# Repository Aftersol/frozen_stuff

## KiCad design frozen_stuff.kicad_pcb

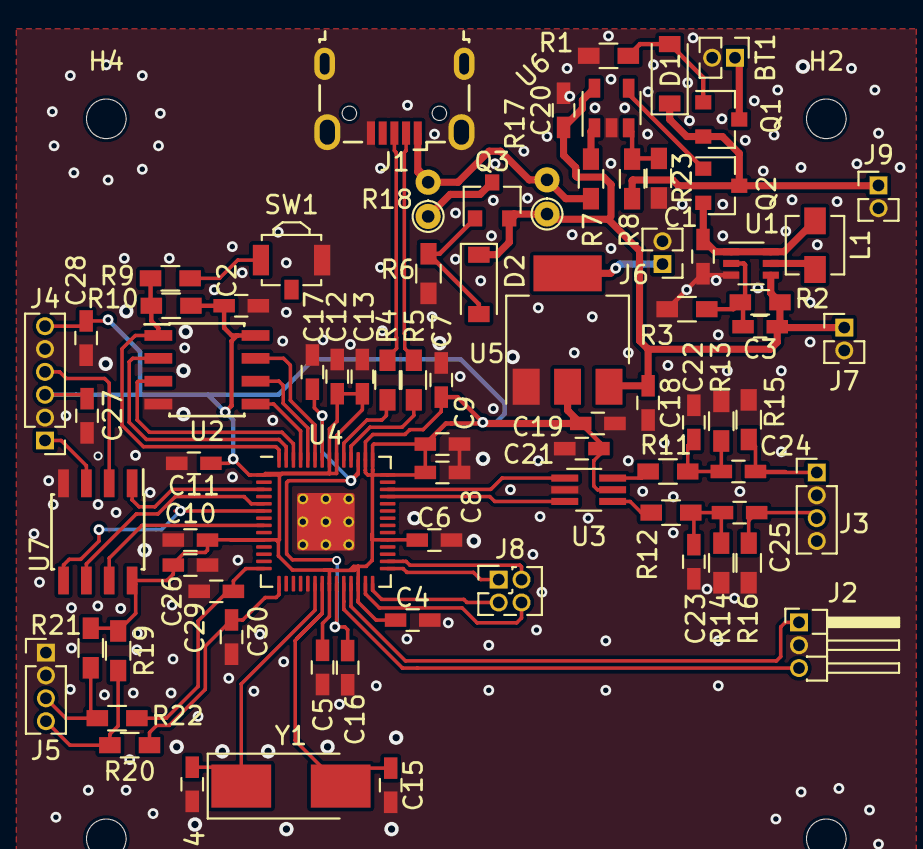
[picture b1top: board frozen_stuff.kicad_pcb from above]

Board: 2 copper layers, 82 parts (0 on the bottom side), 53 nets.

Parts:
BT1: AA; Pin_Header_Straight_1x02_Pitch1.27mm
C1, C3, C18: 10µ; C_0603_HandSoldering
C2, C4, C5, C6, C7, C8, C9, C10, C11, C12, C13, C16, C17, C20, C21, C22, C23, C26, C27, C28, C29, C30: 0.1µ; C_0603_HandSoldering
C14, C15: 22p; C_0603_HandSoldering
C19: 22µ; C_0603_HandSoldering
C24, C25: 47µ; C_0603_HandSoldering
D1, D2: D; D_SOD-123
H1, H2, H3, H4: MountingHole; MountingHole_2.2mm_M2
J1: USB_B_Micro; USB_Micro-B_Wuerth-629105150521
J2: SWD; Pin_Header_Angled_1x03_Pitch1.27mm
J3: Conn_01x04; Pin_Header_Straight_1x04_Pitch1.27mm
J4: Conn_01x06; Pin_Header_Straight_1x06_Pitch1.27mm
J5: Buttons; Pin_Header_Straight_1x04_Pitch1.27mm
J6, J7, J9: Conn_01x02; Pin_Header_Straight_1x02_Pitch1.27mm
J8: Conn_02x02_Top_Bottom; Pin_Header_Straight_2x02_Pitch1.27mm
L1: 4.7µH; L_Vishay_IHLP-1212
Q1, Q2, Q3: NTR2101P; SOT-23
R1, R6, R8, R19, R21, R23: 10K; R_0603_HandSoldering
R2: 0; R_0603_HandSoldering
R3, R10: DNF; R_0603_HandSoldering
R4, R5: 27; R_0603_HandSoldering
R7, R9, R20, R22: 1K; R_0603_HandSoldering
R11, R12: 220; R_0603_HandSoldering
R13, R14: 100; R_0603_HandSoldering
R15, R16: 1.8K; R_0603_HandSoldering
R17: DNF; R_Axial_DIN0204_L3.6mm_D1.6mm_P1.90mm_Vertical
R18: 0; R_Axial_DIN0204_L3.6mm_D1.6mm_P1.90mm_Vertical
SW1: BOOTSEL; SW_SPST_B3U-3100P
U1: TPS61222DCK; Texas_R-PDSO-G6
U2: AT25SF081-SSHD-X; SOIC-8_3.9x4.9mm_Pitch1.27mm
U3: NC7WZ16P6X; SOT-363_SC-70-6_Handsoldering
U4: RP2040; RP2040-QFN-56
U5: AZ1117-3.3; SOT-223-3_TabPin2
U6: LMV321; SOT-23-5
U7: MCP3002; SOIC-8_3.9x4.9mm_Pitch1.27mm
Y1: 12MHz; Crystal_SMD_Abracon_ABM3-2pin_5.0x3.2mm_HandSoldering

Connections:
+1V1: C16.1, C17.1, U4.23, U4.45, U4.50
+1V5: D1.1, J9.1, Q1.2, Q2.3, R8.1
+3V3: C2.1, C4.1, C5.1, C6.1, C7.1, C8.1, C9.1, C10.1, C11.1, C12.1, C13.1, C19.1, C21.1, C26.1, C27.1, C28.1, J4.3, J4.6, J6.1, R10.1, R19.1, R21.1, U2.8, U3.5, U4.1, U4.10, U4.22, U4.26, U4.33, U4.42, U4.43, U4.44, U4.48, U4.49, U5.2, U7.8
+5V: C3.1, C18.1, C20.1, D2.1, J7.1, Q3.2, R2.1, R17.1, U1.4, U5.3, U6.5
/ADC_CS: U4.3, U7.1
/ADC_SCK: U4.8, U7.7
/ADC_SI: U4.6, U7.5
/ADC_SO: U4.5, U7.6
/BUTTON_L: C29.1, R22.1, U4.14
/BUTTON_R: C30.1, R20.1, U4.15
/CS: R9.2, R10.2, U2.1, U4.56
/D+: J1.3, R4.1
/D-: J1.2, R5.1
/GPIO27: U3.3, U4.39
/GPIO28: U3.1, U4.40
/I2C0_SCK: J8.3, U4.28
/I2C0_SDA: J8.4, U4.27
/I2C1_SCK: J8.2, U4.30
/I2C1_SDA: J8.1, U4.29
/IO0: U2.5, U4.53
/IO1: U2.2, U4.55
/IO2: U2.3, U4.54
/IO3: U2.7, U4.51
/Power Supply/CMP_OUT: Q2.1, U6.4
/Power Supply/USBVCC: J1.1, R7.1, R17.2, R18.2
/SCK: U2.6, U4.52
GND: BT1.2, C1.2, C2.2, C4.2, C5.2, C6.2, C7.2, C8.2, C9.2, C10.2, C11.2, C12.2, C13.2, C14.2, C15.2, C16.2, C17.2, C18.2, C19.2, C20.2, C21.2, C22.1, C23.1, C26.2, C27.2, C28.2, C29.2, C30.2, J1.5, J1.6, J2.2, J3.2, J3.4, J4.2, J4.5, J5.1, J5.2, J6.2, J7.2, J9.2, R1.2, R3.2, R6.2, R13.2, R14.2, R15.2, R16.2, R23.2, SW1.2, U1.3, U2.4, U3.2, U4.19, U4.57, U5.1, U6.2, U7.4
unnamed: BT1.1, Q1.3
unnamed: C1.1, L1.1, Q2.2, U1.1, U1.6
unnamed: C3.2, R2.2, R3.1, U1.2
unnamed: C14.1, U4.20, Y1.1
unnamed: C15.1, U4.21, Y1.2
unnamed: C22.2, C24.2, R11.1, R13.1
unnamed: C23.2, C25.2, R12.1, R14.1
unnamed: C24.1, J3.1, R15.1
unnamed: C25.1, J3.3, R16.1
unnamed: D1.2, Q1.1, R1.1
unnamed: D2.2, Q3.1, R6.1
unnamed: J2.1, U4.25
unnamed: J2.3, U4.24
unnamed: J4.1, U7.3
unnamed: J4.4, U7.2
unnamed: J5.3, R21.2, R22.2
unnamed: J5.4, R19.2, R20.2
unnamed: L1.2, U1.5
unnamed: Q3.3, R18.1
unnamed: R4.2, U4.47
unnamed: R5.2, U4.46
unnamed: R7.2, U6.1
unnamed: R9.1, SW1.1
unnamed: R11.2, U3.6
unnamed: R12.2, U3.4
unnamed: R8.2, R23.1, U6.3

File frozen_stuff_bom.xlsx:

Reference | Name | Description | Quanity | Unit Cost | Total Cost | Link | Quanity | Total Cost
U1 | TPS61222DCK | 0.7V to 5V Boost Converter | 1 | 1.54 | 1.54 | https://www.digikey.com/en/products/detail/texas-instruments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 | 3 | 128.73000000000002
U2 | W25Q128JVSIQ | 16MB SPI NOR Flash | 1 | 1.88 | 1.88 | https://www.digikey.com/en/products/detail/winbond-electroni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
U3 | NC7WZ16P6X | PWM Amplifier | 1 | 0.49 | 0.49 | https://www.digikey.com/en/products/detail/onsemi/nc7wz16p6x/673376
U4 | RP2040 | 32-bit MCU | 1 | 1 | 1 | https://www.digikey.com/en/products/detail/raspberry-pi/SC09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
U5 | AZ1117 | 3.3V Regulator | 1 | 0.4 | 0.4 | https://www.digikey.com/en/products/detail/diodes-incorporat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
U6 | LMV321 | Low Power Op Amp | 1 | 0.96 | 0.96 | https://www.digikey.com/en/products/detail/texas-instruments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
U7 | MCP3002 | 10-bit SPI ADC | 1 | 2.17 | 2.17 | https://www.digikey.com/en/products/detail/microchip-technol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
C28,C5,C30,C29,C27,C10,C26,C11,C4,C23,C22,C21,C12,C20,C17,C16,C13,C9,C8,C7,C6,C2 | C0603C104K5RACAUTO7411 | 0.1µ Ceramic Capacitor | 22 | 0.92 | 20.240000000000002 | https://www.digikey.com/en/products/detail/kemet/C0603C104K5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
R23,R21,R19,R8,R6,R1 | CRGCQ0603J10K | 10K Resistors | 6 | 0.1 | 0.60000000000000009 | https://www.digikey.com/en/products/detail/te-connectivity-p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
R22,R20,R9,R7 | CRGCQ0603F1K0 | 1K Resistors | 4 | 0.1 | 0.4 | https://www.digikey.com/en/products/detail/te-connectivity-p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
R5,R4 | CRGCQ0603F27R | 27 Ohm Resistors | 2 | 0.1 | 0.2 | https://www.digikey.com/en/products/detail/te-connectivity-p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
L1 | LQH3NPH4R7MMEL | 4.7µH Inductor | 1 | 0.43 | 0.43 | https://www.digikey.com/en/products/detail/murata-electronic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
Q2,Q3,Q1 | NTR2101PT1G | P-Channel Transistor | 3 | 0.52 | 1.56 | https://www.digikey.com/en/products/detail/onsemi/NTR2101PT1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
D2,D1 | CDBW0520L-G | Schottkey Diode | 2 | 0.4 | 0.8 | https://www.digikey.com/en/products/detail/comchip-technolog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
Y1 | ASFL1-12-000MHZ-EC-T | 12MHz Oscillator | 1 | 1.62 | 1.62 | https://www.digikey.com/en/products/detail/abracon-llc/ASFL1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
C25,C24 | 06036D476MAT2A | 47µ Ceramic Capacitor | 2 | 1.1599999999999999 | 2.3199999999999998 | https://www.digikey.com/en/products/detail/kyocera-avx/06036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
R12,R11 | CRGCQ0603J220R | 220 Ohm Resistors | 2 | 0.1 | 0.2 | https://www.digikey.com/en/products/detail/te-connectivity-p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
R14,R13 | CRGH0603J100R | 100 Ohm Resistors | 2 | 0.1 | 0.2 | https://www.digikey.com/en/products/detail/te-connectivity-p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
R16,R15 | CRGCQ0603F1K8 | 1.8K Resistors | 2 | 0.1 | 0.2 | https://www.digikey.com/en/products/detail/te-connectivity-p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
C15,C14 | CL10C220JB8NNNC | 22pf Ceramic Capacitors | 2 | 0.1 | 0.2 | https://www.digikey.com/en/products/detail/samsung-electro-m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
C18,C3,C1 | GRM188R61E106KA73D | 10µ Ceramic Capacitors | 3 | 0.32 | 0.96 | https://www.digikey.com/en/products/detail/murata-electronic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
R2 | CRCW06030000Z0EAHP | 0 Ohm Resistors | 1 | 0.14000000000000001 | 0.14000000000000001 | https://www.digikey.com/en/products/detail/vishay-dale/CRCW0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
BT1 | Keystone 2463 | Two Cell AA Holder | 1 | 1.29 | 1.29 | https://www.digikey.com/en/products/detail/keystone-electron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
SW1 | B3U-3100P | Tactile Switch | 1 | 0.96 | 0.96 | https://www.digikey.com/en/products/detail/omron-electronics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
J1 | Wurth 629105150521 | Micro USB Connector | 1 | 2.15 | 2.15 | https://www.digikey.com/en/products/detail/w%C3%BCrth-elektr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
